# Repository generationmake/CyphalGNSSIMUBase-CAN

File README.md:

# CyphalGNSSIMUBase-CAN
GNSS and IMU Board for the Raspberry Pi Pico to connect via CAN using OpenCyphal and UCANPHY Micro

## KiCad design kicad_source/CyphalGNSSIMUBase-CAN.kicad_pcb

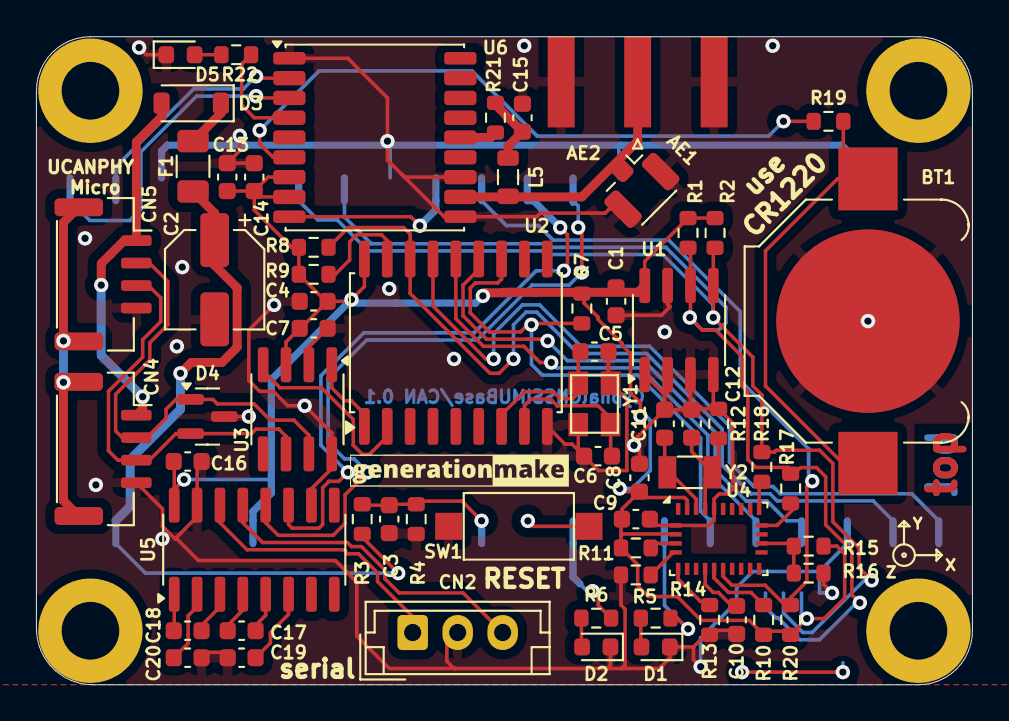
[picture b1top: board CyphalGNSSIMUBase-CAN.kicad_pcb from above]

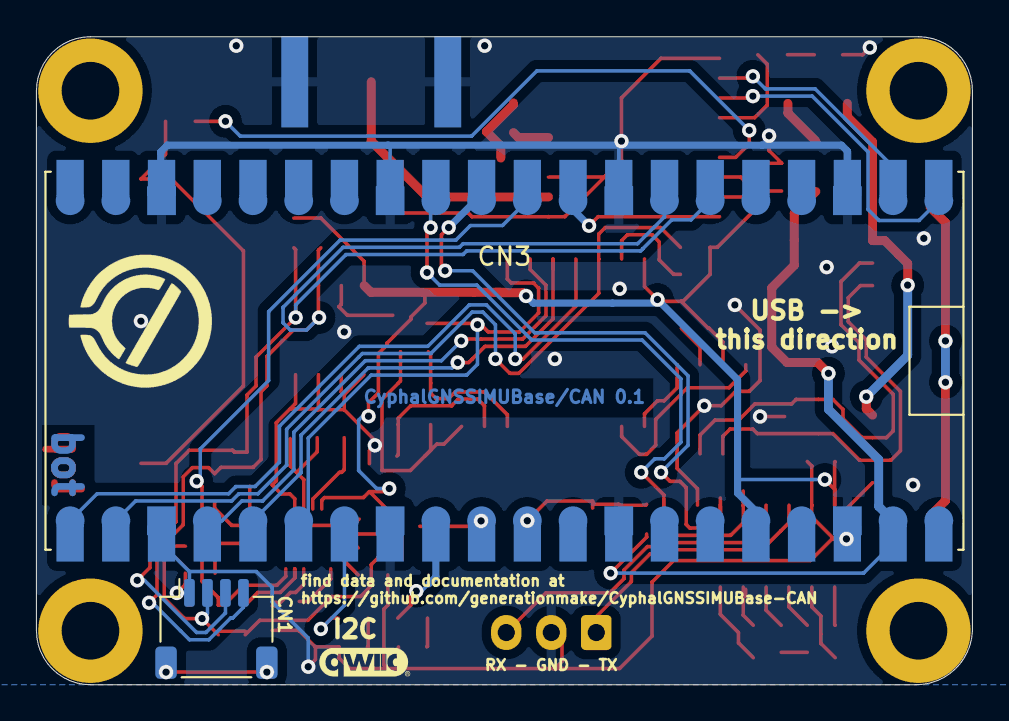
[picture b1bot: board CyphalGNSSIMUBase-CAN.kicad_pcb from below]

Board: 2 copper layers, 52.0 x 36.0 mm, 74 parts (5 on the bottom side), 57 nets.

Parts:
AE1: Antenna_Shield; U.FL_Hirose_U.FL-R-SMT-1_Vertical
AE2: Antenna_Shield; SMA_Amphenol_132289_EdgeMount
BT1: Battery_Cell; BatteryHolder_Keystone_3000_1x12mm
C1, C3, C4, C7, C8, C9, C10, C16, C17, C18, C19, C20: 100nF; C_0603_1608Metric
C2: 100 uF / 6,3 V; CP_Elec_5x5.3
C5, C6: 10pF; C_0603_1608Metric
C11, C12: 22pF; C_0603_1608Metric
C13, C14, C15: 100 nF; C_0603_1608Metric
CN1: SM04B-SRSS-TB; JST_SH_SM04B-SRSS-TB_1x04-1MP_P1.00mm_Horizontal
CN2: Conn_01x03; JST_EH_B3B-EH-A_1x03_P2.50mm_Vertical
CN3: RASPBERRYPI_PICO; RASPI_PICO_SOLDER_ONLY
CN4, CN5: SM04B-GHS-TB; JST_GH_SM04B-GHS-TB_1x04-1MP_P1.25mm_Horizontal
D1: KT-0603R; LED_0603_1608Metric
D2: NCD0603Y1; LED_0603_1608Metric
D3: MBR0530T; D_SOD-123
D4: DNI; SOT-23
D5: LED_Small; LED_0603_1608Metric
F1: nSMD050-33V; Fuse_1206_3216Metric
L1: Label; generationmake_small_silk
L2: Label; generationmake_small_solder
L3: Label; opencyphal_small
L4: Label; qwiic_logo
L5: L; L_0805_2012Metric
MECH1, MECH2, MECH3, MECH4: MHP_3.2_5.8
R1, R2, R4, R7, R8, R9, R11, R20: 10k; R_0603_1608Metric
R3: 100k; R_0603_1608Metric
R5, R6: 3k3; R_0603_1608Metric
R10, R12, R13, R14, R16: 0R; R_0603_1608Metric
R15, R17, R18: DNI; R_0603_1608Metric
R19, R21, R22: 1k; R_0603_1608Metric
SW1: PTS636 SM43 SMTR LFS; SW_SPST_CK_RS282G05A3
U1: M24C64-RMN6TP; SOIC-8_3.9x4.9mm_P1.27mm
U2: MCP2515T-I/SO; SOIC-18W_7.5x11.6mm_P1.27mm
U3: SN65HVD230; SOIC-8_3.9x4.9mm_P1.27mm
U4: BNO085; LGA-28_5.2x3.8mm_P0.5mm
U5: MAX3232; SOIC-16_3.9x9.9mm_P1.27mm
U6: MAX-M10S; ublox_MAX
Y1: X322516MLB4SI; Crystal_SMD_3.2x2.5mm_4Pad
Y2: DNI; Crystal_SMD_3215-2Pin_3.2x1.5mm

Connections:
+3V3: C1.1, C4.1, C7.1, C8.1, C9.1, C13.1, C14.1, C16.1, CN1.2, CN3.36 (3V3(OUT)), R1.1, R2.1, R7.1, R8.1, R9.1, R10.1, R11.1, R15.1, R20.1, U1.8 (VCC), U2.18 (VDD), U3.3 (VCC), U4.3 (VDD), U4.28 (VDDIO), U5.16 (VCC), U6.7 (VCC_IO), U6.8 (VCC)
+BATT: C2.1, CN3.39 (VSYS), F1.1, R3.1
/+BATT_MEAS: C3.1, CN3.31 (GP26/ADC0/I2C1_SDA), R3.2, R4.1
/BNO085/BNO085_H_MISO: R18.1, U4.20 (H_SDA/H_MISO/TX)
/BNO085/BNO085_H_MOSI: R15.2, R16.1, U4.17 (SA0/H_MOSI)
/BNO085/BNO085_H_SCK: R17.1, U4.19 (H_SCL/SCK/RX)
/BNO085/BOOTN: R11.2, U4.4 (BOOTN)
/BNO085/CAP: C10.1, U4.9 (CAP)
/BNO085/CLKSEL0: R10.2, U4.10 (CLKSEL0)
/BNO085/CLKSEL1: C12.1, R12.1, U4.26 (XOUT32/CLKSEL1), Y2.2
/BNO085/PS0: R13.1, U4.6 (PS0/WAKE)
/BNO085/PS1: R14.1, U4.5 (PS1)
/BNO085/XIN32: C11.1, U4.27 (XIN32), Y2.1
/GNSS/D5_R: D5.2 (A), R22.2
/GNSS/NEO_ANTENNA: AE1.1 (A), AE2.1 (A), L5.2, U6.11 (RF_IN)
/GNSS/TIMEPULSE: R22.1, U6.4 (TIMEPULSE)
/GNSS/VCC_RF: R21.1, U6.14 (VCC_RF)
/GNSS/VCC_RF_R: C15.1, L5.1, R21.2
/GNSS/V_BCKP: R19.2, U6.6 (V_BCKP)
/GNSS/V_BCKP_R: BT1.1 (+), R19.1
/LED2: CN3.27 (GP21/I2C0_SCL), R5.1
/LED2_R: D1.2 (A), R5.2
/LED3: CN3.29 (GP22), R6.1
/LED3_R: D2.2 (A), R6.2
/MCP2515/CANH: CN4.2, CN5.2, D4.1 (K), U3.7 (CANH)
/MCP2515/CANL: CN4.3, CN5.3, D4.2 (K), U3.6 (CANL)
/MCP2515/CANVCC: CN4.1, CN5.1, D3.2 (A)
/MCP2515/MCP2515_OSC1: C6.1, U2.8 (OSC1), Y1.3
/MCP2515/MCP2515_OSC2: C5.1, U2.7 (OSC2), Y1.1
/MCP2515/MCP2515_RESET: R9.2, U2.17 (RESET#)
/MCP2515/MP1: CN4.MP (MountPin), CN5.MP (MountPin)
/MCP2515/RXCAN: U2.2 (RXCAN), U3.4 (R)
/MCP2515/TXCAN: U2.1 (TXCAN), U3.1 (D)
/RESET: CN3.30 (RUN), SW1.1
/RS232_C1+: C18.1, U5.1 (C1+)
/RS232_C1-: C18.2, U5.3 (C1-)
/RS232_C2+: C17.1, U5.4 (C2+)
/RS232_C2-: C17.2, U5.5 (C2-)
/RS232_RX: CN2.3, U5.13 (R1IN)
/RS232_TX: CN2.1, U5.14 (T1OUT)
/SERIAL2_RX: CN3.12 (GP9/SPI1_CS/I2C0_SCL/UART1_RX), U5.12 (R1OUT)
/SERIAL2_TX: CN3.11 (GP8/SPI1_RX/I2C0_SDA/UART1_TX), U5.11 (T1IN)
BNO_RESET: CN3.10 (GP7/SPI0_TX/I2C1_SCL), R20.2, U4.11 (NRST)
GND: AE1.2 (Shield), AE2.2 (Shield), BT1.2 (-), C1.2, C2.2, C3.2, C4.2, C5.2, C6.2, C7.2, C8.2, C9.2, C10.2, C11.2, C12.2, C13.2, C14.2, C15.2, C16.2, C19.2, C20.2, CN1.1, CN2.2, CN3.3 (GND), CN3.8 (GND), CN3.13 (GND), CN3.18 (GND), CN3.23 (GND), CN3.28 (GND), CN3.33 (GND/AGND), CN3.38 (GND), CN4.4, CN5.4, D1.1 (K), D2.1 (K), D4.3 (A), D5.1 (K), R4.2, R12.2, R13.2, R14.2, R16.2, SW1.2, U1.1 (A0), U1.2 (A1), U1.3 (A2), U1.4 (VSS), U1.7 (WP), U2.9 (VSS), U3.2 (GND), U3.8 (NC1), U4.2 (GND), U4.25 (GNDIO), U5.10 (T2IN), U5.15 (GND), U6.1 (GND), U6.10 (GND), U6.12 (GND), Y1.2 (case), Y1.4 (case)
GNSS_RESET: CN3.9 (GP6/SPI0_SCK/I2C1_SDA), U6.9 (~RESET)
I2C_SCL: CN1.4, CN3.7 (GP5/SPI0_CS/I2C0_SCL/UART1_RX), R1.2, R17.2, U1.6 (SCL)
I2C_SDA: CN1.3, CN3.6 (GP4/SPI0_RX/I2C0_SDA/UART1_TX), R2.2, R18.2, U1.5 (SDA)
MCP2515_CS: CN3.22 (GP17/SPI0_CS/I2C0_SCL/UART0_RX), R8.2, U2.16 (CS#)
MCP2515_INT: CN3.26 (GP20/I2C0_SDA), R7.2, U2.12 (INT)
MISO: CN3.21 (GP16/SPI0_RX/I2C0_SDA/UART0_TX), U2.15 (SO)
MOSI: CN3.25 (GP19/SPI0_TX/I2C1_SCL), U2.14 (SI)
unnamed: D3.1 (K), F1.2
unnamed: C20.1, U5.2 (VS+)
unnamed: C19.1, U5.6 (VS-)
SCK: CN3.24 (GP18/SPI0_SCK/I2C1_SDA), U2.13 (SCK)
SERIAL1_RX: CN3.2 (GP1/SPI0_CS/I2C0_SCL/UART0_RX), U6.2 (TXD)
SERIAL1_TX: CN3.1 (GP0/SPI0_RX/I2C0_SDA/UART0_TX), U6.3 (RXD)

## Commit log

2026-05-24 copied files from CyphalPicoBase/CAN
2026-05-24 removed unnecessary parts
2026-05-24 added BNO085
2026-05-25 added GNSS u-blox max-m10
2026-05-25 generated pdf schematic
2026-05-25 added RS232 level shifter
2026-05-25 added battery holder for GNSS backup
2026-05-25 connected reset of BNO055 and GNSS module, updated layout
2026-05-25 updated layout
2026-05-25 fixed some drc errors
2026-05-25 updated schematic pdf
2026-05-25 fixed drc errors
